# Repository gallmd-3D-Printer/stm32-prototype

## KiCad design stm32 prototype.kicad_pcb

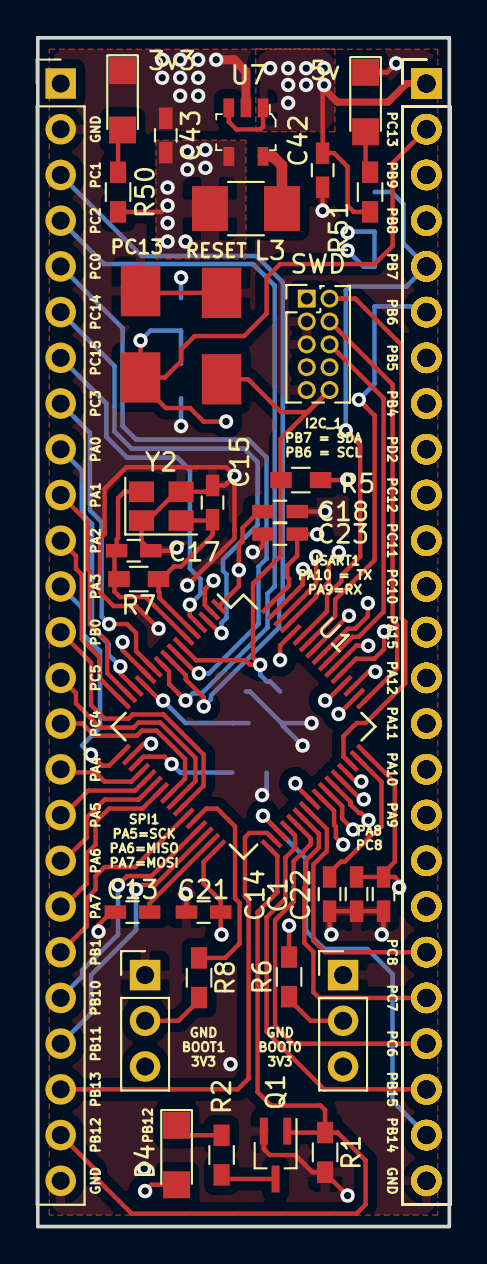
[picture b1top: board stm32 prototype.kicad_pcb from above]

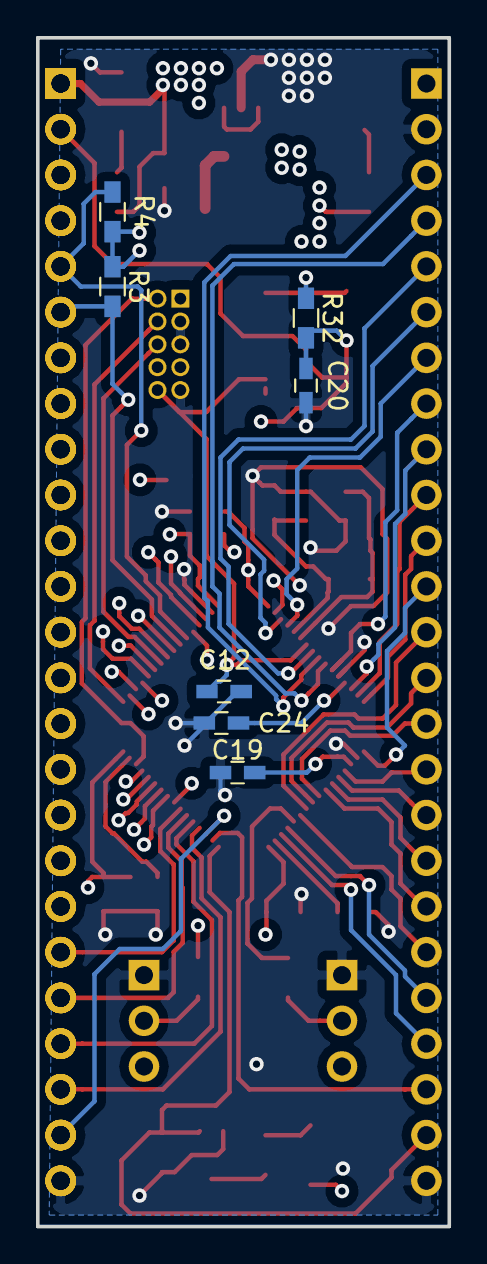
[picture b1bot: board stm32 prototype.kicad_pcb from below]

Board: 4 copper layers, 22.9 x 66.0 mm, 43 parts (7 on the bottom side), 65 nets.

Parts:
3v3, 5v: LED; LED_1206
C1, C42: 4.7uF; C_0603_HandSoldering
C12, C20: 0.1uF; C_0603_HandSoldering
C13, C14: 2.2uF; C_0603_HandSoldering
C15, C17: 9pF; C_0603_HandSoldering
C18, C19, C21, C22, C23, C24: .1uF; C_0603_HandSoldering
C43: 10uF; C_0603_HandSoldering
D4: LED; LED_1206
J1, J1#2, J1#3, J8: Conn_01x25; Pin_Header_Straight_1x25_Pitch2.54mm
J9, J10: Conn_01x03; Pin_Header_Straight_1x03_Pitch2.54mm
L3: 10uH; L_1210_HandSoldering
PC13: SW_Push; FSM2JMTR
Q1: Q_NMOS_GSD; SOT-323_SC-70_Handsoldering
R1, R3, R4: 10K; R_0603_HandSoldering
R2, R50, R51: 330R; R_0603_HandSoldering
R5, R6, R8, R32: 10k; R_0603_HandSoldering
R7: 1MR; R_0603_HandSoldering
RESET: SW_Push; FSM2JMTR
SWD: Conn_02x05_Odd_Even; Pin_Header_Straight_2x05_Pitch1.27mm
U1: STM32F405RGTx; LQFP-64_10x10mm_Pitch0.5mm
U7: TPS62203DBVR; SOT-753
Y2: Crystal_GND24; Crystal_SMD_SeikoEpson_TSX3225-4pin_3.2x2.5mm

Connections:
+3V3: C1.2, C18.2, C19.2, C21.2, C22.2, C23.2, C24.2, C43.1, D4.2, J8.1, J9.3, J10.3, L3.1, R3.1, R4.1, R5.1, R32.1, R50.1, SWD.1, U1.1, U1.13, U1.19, U1.32, U1.48, U1.64, U7.4
+5V: C42.1, J1.1, J1#2.1, J1#3.1, R51.1, U7.1, U7.3
GND: 3v3.1, 5v.1, C1.1, C12.1, C13.1, C14.1, C15.2, C17.2, C18.1, C19.1, C20.1, C21.1, C22.1, C23.1, C24.1, C42.2, C43.2, J1.25, J1#2.25, J1#3.25, J8.2, J8.25, J9.1, J10.1, PC13.2, Q1.2, R1.2, RESET.2, SWD.3, SWD.5, SWD.9, U1.12, U1.18, U1.63, U7.2, Y2.1, Y2.3
NRST: C12.2, R5.2, RESET.1, SWD.10, U1.7
unnamed: C13.2, U1.31
unnamed: C14.2, U1.47
unnamed: C15.1, R7.1, U1.5, Y2.2
unnamed: C17.1, R7.2, U1.6, Y2.4
unnamed: D4.1, R2.1
unnamed: 3v3.2, R50.2
unnamed: 5v.2, R51.2
unnamed: J9.2, R6.2
unnamed: J10.2, R8.2
unnamed: L3.2, U7.5
unnamed: Q1.3, R2.2
unnamed: R6.1, U1.60
unnamed: R8.1, U1.28
PA0: J8.9, U1.14
PA1: J8.10, U1.15
PA2: J8.11, U1.16
PA3: J8.12, U1.17
PA4_SPI1_NSS: J8.16, U1.20
PA5_SPI1_SCK: J8.17, U1.21
PA6_SPI1_MISO: J8.18, U1.22
PA7_SPI1_MOSI: J8.19, U1.23
PA8_MCO: J1.18, J1#2.18, J1#3.18, U1.41
PA9_ST_RXD: J1.17, J1#2.17, J1#3.17, U1.42
PA10_ST_TXD: J1.16, J1#2.16, J1#3.16, U1.43
PA11_ST_RTS: J1.15, J1#2.15, J1#3.15, U1.44
PA12_CTS: J1.14, J1#2.14, J1#3.14, U1.45
PA15: J1.13, J1#2.13, J1#3.13, U1.50
PB0: J8.13, U1.26
PB1: J8.20, U1.27
PB4: J1.8, J1#2.8, J1#3.8, U1.56
PB5_I2C1_SMBA: J1.7, J1#2.7, J1#3.7, U1.57
PB6_I2C1_SCL: J1.6, J1#2.6, J1#3.6, R3.2, U1.58
PB7_I2C1_SDA: J1.5, J1#2.5, J1#3.5, R4.2, U1.59
PB8: J1.4, J1#2.4, J1#3.4, U1.61
PB9: J1.3, J1#2.3, J1#3.3, U1.62
PB10: J8.21, U1.29
PB11: J8.22, U1.30
PB12: J8.24, Q1.1, R1.1, U1.33
PB13: J8.23, U1.34
PB14: J1.24, J1#2.24, J1#3.24, U1.35
PB15: J1.23, J1#2.23, J1#3.23, U1.36
PC0: J8.5, U1.8
PC1: J8.3, U1.9
PC2: J8.4, U1.10
PC3: J8.8, U1.11
PC4: J8.15, U1.24
PC5: J8.14, U1.25
PC6: J1.22, J1#2.22, J1#3.22, U1.37
PC7: J1.21, J1#2.21, J1#3.21, U1.38
PC8: J1.20, J1#2.20, J1#3.20, U1.39
PC9: J1.19, J1#2.19, J1#3.19, U1.40
PC10: J1.12, J1#2.12, J1#3.12, U1.51
PC11: J1.11, J1#2.11, J1#3.11, U1.52
PC12: J1.10, J1#2.10, J1#3.10, U1.53
PC13: C20.2, J1.2, J1#2.2, J1#3.2, PC13.1, R32.2, U1.2
PC14: J8.6, U1.3
PC15: J8.7, U1.4
PD2: J1.9, J1#2.9, J1#3.9, U1.54
SWO: SWD.6, U1.55
TCK_SWCLK: SWD.4, U1.49
TMS_SWDIO: SWD.2, U1.46

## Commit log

2018-11-21 fixed SWD header for STM32
2018-11-22 worked on some layout
2018-11-24 laid out usb input section
2018-11-27 added switcher to 3.3v rail, began layout of 3.3v regulator
2018-11-28 worked on some layout around the stm32f
2018-11-29 laid out reserve linear 3.3V regulator, wired up FTDI header
2018-12-01 laid out crystal oscilator, connected binary indicator leds
2018-12-05 worked on stm flash chip layout, stm bypass capacitor layout, changed antenna connection to sma
2018-12-06 did a little layout around esp32, need to check pinout of stm crystal, need to check trace width and spacing for esp32
2018-12-10 began switching to esp32-wroom module
2018-12-12 added push button to stm32, worked on some layout
2018-12-13 worked on layout, created board outline, started working on fitting the input, esp32, and stm32 sections together
2018-12-14 reworked layout of esp32 section
2018-12-16 layout almost done, changing my mind, getting rid of esp32, usb section
2018-12-27 Ordered PCB 12/18
2018-12-28 began simplifying, switching to STM32F405 series
2018-12-28 pushed change to stm32f405 to pcb
2018-12-31 Worked on layout for new MCU
2019-01-03 finished layout, need to do final review before ordering PCB
2019-01-17 Ordered PCB from OSHPark
